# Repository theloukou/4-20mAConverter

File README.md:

# 4-20mAConverter
4-20mA to Voltage

Simple PCB to convert 4-20mA signals to voltage, to feed in MCU ADC.
Jumper selects output scaled better for 3.3 or 5 Volt systems.

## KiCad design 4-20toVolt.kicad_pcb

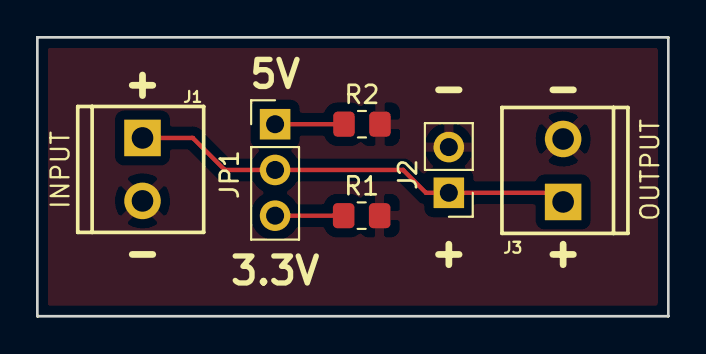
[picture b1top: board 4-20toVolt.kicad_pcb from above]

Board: 2 copper layers, 35.1 x 15.5 mm, 6 parts (0 on the bottom side), 4 nets.

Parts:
J1: INPUT; SCREWTERMINAL-3.5MM-2
J2: OUTPUT; PinHeader_1x02_P2.54mm_Vertical
J3: OUTPUT; SCREWTERMINAL-3.5MM-2
JP1: Jumper_3_Bridged12; PinHeader_1x03_P2.54mm_Vertical
R1: 120R; R_0805_2012Metric_Pad1.20x1.40mm_HandSolder
R2: 200R; R_0805_2012Metric_Pad1.20x1.40mm_HandSolder

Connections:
GND: J1.2, J2.2, J3.2, R1.2, R2.2
unnamed: J1.1, J2.1, J3.1, JP1.2
unnamed: JP1.1, R2.1
unnamed: JP1.3, R1.1

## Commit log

2021-09-29 1st commit
